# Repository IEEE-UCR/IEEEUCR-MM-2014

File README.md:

IEEEUCR-MM-2014
===============

In order to create better, exciting micromice, it is necessary to pool together work in order to create better programs to run on micromice.

This repository has folders for all current micromice.  Some may have been abandoned in favor of better mice (refmouse V1).

Although it is difficult to admit to the utter data-copying, a lot of the kicad libraries are copied.

Within the hardware realm, KiCAD is the de facto standard for making PCBs.  When micromice get really big, it's absolutely essential to choose a program that allows multipage schematics.

And through these methods, we will create better micromice.

Documentation is also provided through the documentation folder... in case anybody wants to read it.

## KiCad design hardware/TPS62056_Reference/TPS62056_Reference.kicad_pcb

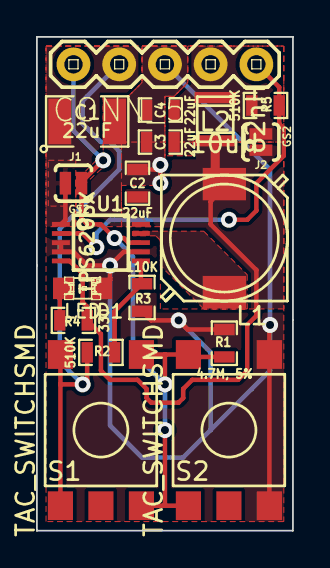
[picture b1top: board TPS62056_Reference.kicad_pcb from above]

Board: 2 copper layers, 14.2 x 27.4 mm, 18 parts (0 on the bottom side), 9 nets.

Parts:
C1: 22uF; SM1210
C2, C3, C4: 22uF; SM0603_Capa
D1: LED; LED-0805
J1, J2: GS2; SparkFun-SJ_2S-NO
L1: 10uH; Bourns_SRR7032
L2: 82nH; Bourns_PM1008
P1: CONN_5; SparkFun-1X05
R1: 4.7M, 5%; SM0603_Resistor
R2, R5: 510K; SM0603_Resistor
R3: 110K; SM0603_Resistor
R4: 330; SM0603_Resistor
S1, S2: TAC_SWITCHSMD; Alps_TACT_SKHM_Series
U1: TPS6205X; MSOP10-0.5

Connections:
+BATT: C1.1, J1.1, P1.2, R2.1, S1.3, S1.4, U1.1
/EN: J1.2, P1.1, R1.1, S1.1, S1.2, S2.3, S2.4, U1.8
/FB: C2.1, J2.1, L1.2, L2.1, R4.1, U1.5
/LBI: R2.2, R3.1, U1.6
/LBO: P1.5, R5.2, U1.2
/SW: L1.1, U1.9
/VOUT: C3.1, C4.1, J2.2, L2.2, P1.4, R5.1
GND: C1.2, C2.2, C3.2, C4.2, D1.2, P1.3, R1.2, R3.2, S2.1, S2.2, U1.3, U1.4, U1.7, U1.10
unnamed: D1.1, R4.2

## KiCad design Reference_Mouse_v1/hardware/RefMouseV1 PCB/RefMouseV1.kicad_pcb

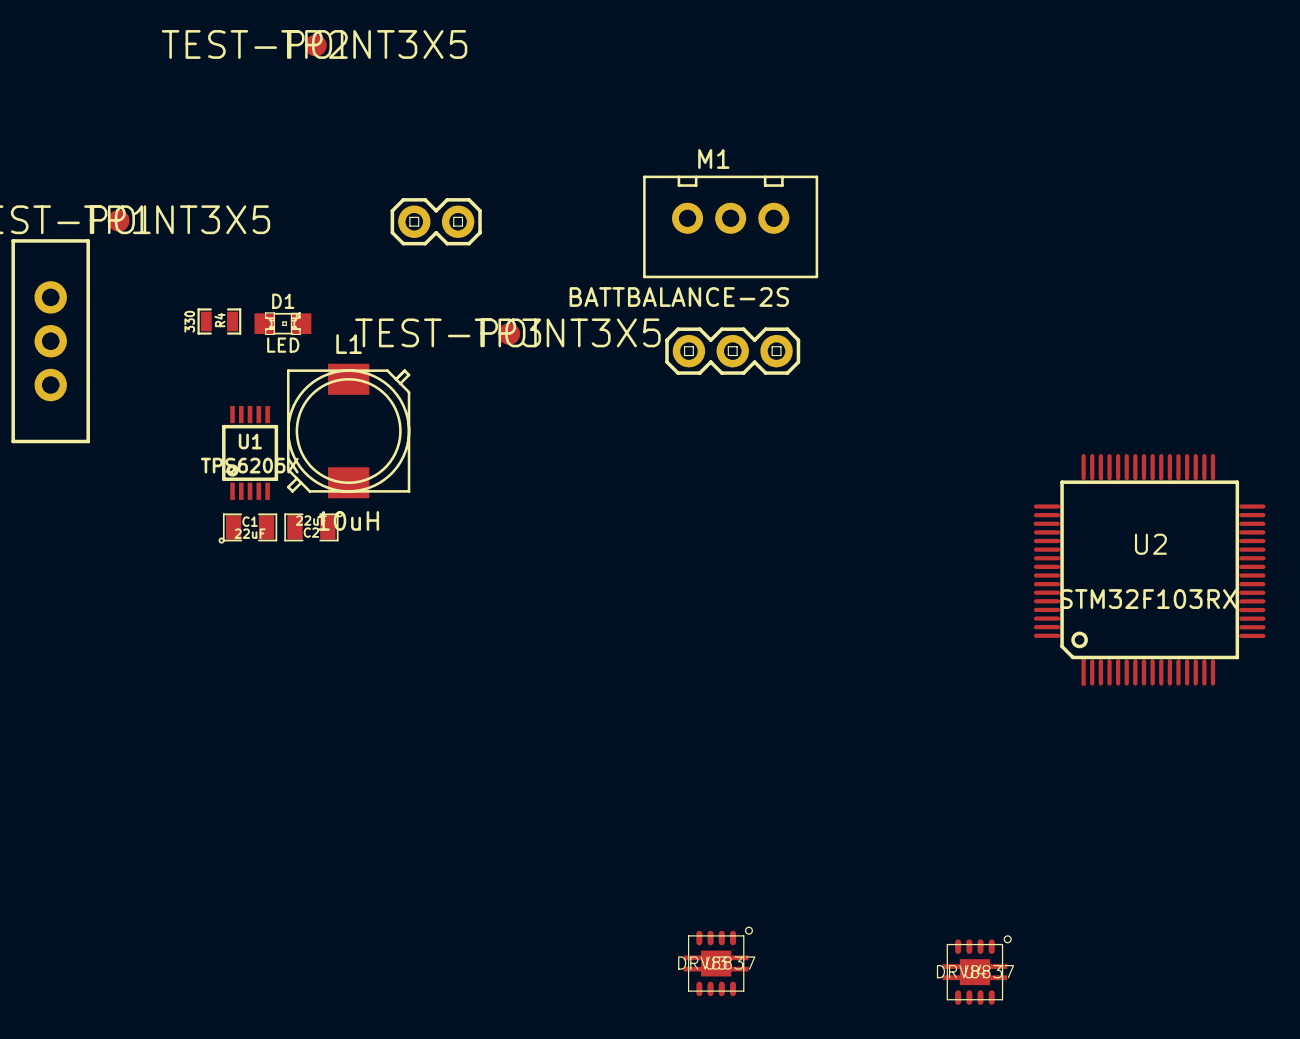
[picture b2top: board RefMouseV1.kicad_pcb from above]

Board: 2 copper layers, 16 parts (0 on the bottom side), 9 nets, no tracks yet.

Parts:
C1, C2: 22uF; SM0805
D1: LED; LED-0805
JP1: M03PTH; SparkFun-1X03
JP2: M02PTH; SparkFun-1X02
L1: 10uH; Bourns_SRR7032
M1: BATTBALANCE-2S; B3B-XH-A
R4: 330; SM0603_Resistor
S1: SWITCH-SPSTPTH; SparkFun-SWITCH-SPDT
TP1, TP2, TP3: TEST-POINT3X5; SparkFun-PAD.03X.05
U1: TPS6205X; MSOP10-0.5
U2: STM32F103RX; TQFP_64
U3, U4: DRV8837; S-PWSON-N8

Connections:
/Motor/V_LOGIC: U3.7, U3.8, U4.7, U4.8
/Motor/V_MOTOR: U3.1, U4.1
/Power/+3.3V: C2.1, L1.2, R4.1, U1.5
/Power/SW: L1.1, U1.9
/Power/VBATT: C1.1, JP1.3, M1.3, S1.1, U1.1
/Power/VBATT_SW: S1.2, U1.8
GND: C1.2, C2.2, D1.2, JP1.1, JP2.1, JP2.2, M1.1, S1.3, U1.3, U1.4, U1.6, U1.7, U1.10, U2.63, U3.4, U4.4
unnamed: D1.1, R4.2
unnamed: JP1.2, M1.2

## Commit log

2013-06-06 I added a bit of the directory structure and improved the readme a bit.e
2013-06-06 Accidental problems fixed. Sorry for all the commits.
2013-06-06 I added my crappy code. Feel free to make it not work any more. The functions are not yet set in stone.
2013-06-06 Added some documentation for encoder control.
2013-07-20 Added power supply schematic and link to more mouse code
2013-07-23 Found parts, created footprints, added to board.
    Board had all footprints on it, but it completely rat's nest.
    Spreadsheet BOM created, but not yet in repo.
2013-07-24 Board is almost completely routed
    Except for an error that prevents me from connecting anything to the
    IC...
2013-07-24 Board completed
    Added silkscreen help and connected the rest of the pins
2013-07-24 Added BOM
2013-07-24 Fixed some minor errors in BOM
2013-07-24 Added more via stitching and gerbers
    More via stitching between front & back ground plane and adjusted planes
    to fit vias.
2013-07-24 Moved silkscreen to so that it's not broken by vias. Added PDF of schem and board.
2013-07-24 Added SVG plots of board
2013-08-08 I finally did something: add documentation and begin creating some of the interfaces to the STM32 chip.
2013-08-10 So, I removed the extra files and added a few more that are relevant to our micromouse.
2013-08-10 OKAY, NOW I REMOVED THE FILES.
2013-08-11 Wrong datasheet. Sorry.
2013-08-17 Oshpark board preview
2013-08-26 RefMouse1 stuff
    Added datasheets and started schematic
2013-08-28 Added Motor Driver
2013-09-04 More reference mouse pcb stuff
2013-09-17 Added gearbox.
2013-09-19 mount rev2: changed dimensions around and mountin
2013-09-21 Moved 3D modeling into reference mouse v1 folder.
    Added McMasterCarr parts.
2013-10-05 More 3D modeling done!
2013-10-08 More editing!
2013-10-08 Added DRV sch symbol and motor sub-schematic.
2013-10-08 I tried... the structs come in pretty soon...
2013-10-10 Generated STL files (most are not critical) Updated micromouse code a bit (far from done)
2013-10-10 Cleaned up files... I don't want to upload all of THAT!
2013-10-22 I changed the readme because Brandon is awesome!
2013-11-15 Added Sensors in AutoCad
2014-04-06 Added datasheets for components in FPGA mouse
    DE0-Nano schematics and datasheets, LY3200 gyro, moved connector
    datasheet
2014-04-18 Added datasheets
2014-04-18 Added datasheets and folders for reference mouse v2
2014-04-18 Rearranged folder structure so that projects are top-level
2014-04-18 Removed old directory structure
2014-04-19 Moved a datasheet.
2014-04-21 Began development on FPGA mouse board internals.
    This seems difficult.
2014-04-21 Added all FPGA parts and updated excel sheet of pinout.
2014-04-21 Commiting with corrected file paths
2014-04-22 Schematic things have been updated
2014-04-23 A lot of kicad.... A LOT.
2014-04-23 Did a 3D drivetrain on refmouse 2
2014-04-24 Made changes to board 20% done still. :/
2014-04-24 Changed DRV8837, Almost completed main board. ERC almost successful.
2014-04-24 Changed directory structure, where did the fpga board go?
2014-04-24 re-added the fpga parts... I wonder where everything went o.0
2014-04-24 Removed that pesky noname.pro file.
2014-04-24 Finalized connector structure.
2014-04-24 Okay, now the connector is finalized.
2014-04-24 Git says some inventor files changed, so here
2014-04-24 Flipped some RGB leds, added emitter pulldowns
2014-04-24 Repopulated FPGA portions...
    Where did my changes go?
2014-04-24 Added bank names to FPGA
2014-04-26 Added ESD prevention documentation.
    Added ByteBlaster documentation.
    Modified FPGA banks.
2014-04-26 Deleted the noname file that kicad loves generating.
2014-04-26 Modified documentation.
2014-04-26 Added DAC and amp.
    Changed connector spec. for DAC and amp. Sorry guys.
2014-04-26 Did a bit of schematic labeling.
2014-04-26 Removed backup files and added backup files to git exclude.
    Also added FPGA processor (not done yet).
2014-04-27 Created I2C component (will be changed later because of errors).
    Add I2C to board connector on main board (daughter board yet to be done).
2014-04-28 Updated schematic and added craptons of symbols.
2014-04-29 Updated schematics
2014-04-30 Reverted Refmouse2 Spacer to original size
2014-05-03 Made changes that I forgot about... sorry guys
2014-05-03 Moved around Overvolt software. Preparing for massive software rewriting.
2014-05-10 Made wheel bigger on RefMouse2
2014-05-10 MAde D-shaft on wheel larger
2014-05-10 Added some PCB drilling notes
2014-05-11 Committing the few things that have been changed these weeks
2014-05-11 Deleted extra project file. Darn it, kicad.
2014-05-11 Changed things
2014-05-11 Added remote control capabilities to mouse
